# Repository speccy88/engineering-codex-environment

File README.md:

# Engineering CAD & EDA Workbench

A native Debian 13 toolchain for **ChatGPT / Codex Cloud engineering tasks**: create editable circuits and PCBs, model mechanical parts and enclosures, simulate electrical behavior, and return drawings, renders and project files through chat.

**[Showcase](#project-showcase-555-led-fader) · [Example prompts](#example-prompts-by-workflow) · [Run the tools](#use-an-installed-environment) · [Setup](#installation-and-cloud-publication) · [Validation](#verified-behavior)**

## Project showcase: 555 LED fader

An existing six-LED timer project demonstrates how the tools work together: a KiCad schematic and routed PCB, ngspice waveforms, a fitted FreeCAD enclosure, and assembly renders.

<table>
<tr>
<td width="50%"></td>
<td width="50%"></td>
</tr>
<tr><td><b>Electronic assembly</b><br>5 V supply, NE555 timer, transistor driver and six LEDs on a 70 × 54 mm PCB.</td><td><b>Mechanical integration</b><br>86 × 70 × 23 mm enclosure with PCB standoffs, a screw-fastened lid and aligned LED openings.</td></tr>
</table>

These images come from the owner's earlier **555 LED Fader Design Files** and **555 LED Fader Enclosure** projects. The design was reconstructed from photographs; circuit values and dimensions include assumptions. Prior project checks reported zero KiCad ERC/DRC errors and zero PCB/enclosure CAD intersections. It has **not been physically tested or test-fitted**. [Image provenance and reproduction notes](docs/showcase/README.md) distinguish those existing results from the new examples below.

## Example prompts by workflow

Copy a prompt into an installed cloud environment and attach any existing design files. Specify dimensions, units, supply voltage, manufacturing constraints and preferred formats where relevant. Each workflow can be used independently.

### Schematics, PCB layout and routing

**KiCad · SKiDL · Freerouting** — editable schematics and boards, component placement, routing, electrical/design-rule checks, fabrication files and assembled STEP exports.

```text
Design a 5 V, six-LED fader using a 555 timer and a transistor driver.
Use a 70 × 54 mm two-layer PCB with through-hole components. Draw a clean
schematic with readable labels and no overlapping symbols. Explain the
component choices and assumptions, route the board, and run ERC, DRC and
schematic/PCB net checks. Return the editable KiCad project, Gerbers, drill
files, BOM, assembled STEP, preview images and a validation report in a ZIP.
```

For an existing board, ask to preserve its outline, connectors and design rules. Freerouting supplies a DSN → SES routing workflow; imported routes must still pass KiCad checks. [EDA workflow](docs/eda.md)

### Fritzing projects and custom components

**Fritzing · Python layout generator** — self-contained `.fzz` projects, `.fzpz` custom parts, schematic/breadboard/PCB views, native renders and Gerber/drill export.

<table>
<tr>
<td width="50%"></td>
<td width="50%"></td>
</tr>
<tr><td>Breadboard view</td><td>Routed PCB view</td></tr>
</table>

```text
Create a Fritzing project for a 5 V connector, a 330 ohm resistor and a red
LED. Use through-hole parts and a single copper layer. Generate any custom
parts with explicit pin mappings. Keep symbols and labels clear, route
around obstacles, and check overlaps, route clearances and connectivity.
Return the design JSON, editable FZZ, FZPZ parts, PNG/SVG previews of all
three views, Gerber/drill files and the validation report.
```

Try the checked-in [editable project](examples/fritzing/verified/led-series.fzz) or [complete example bundle](examples/fritzing/verified/led-series.zip). The generator supports a documented through-hole, single-layer subset. Its layout checks are **not native Fritzing DRC or electrical ERC**; a schematic-style breadboard view is not a verified physical breadboard assembly. [Fritzing workflow and limits](docs/fritzing.md)

### Parametric parts and PCB enclosures

**FreeCAD · CadQuery · build123d · OpenSCAD** — constrained sketches, editable parameters, solid modeling, STEP/STL export and geometry checks.

<table>
<tr>
<td width="50%"></td>
<td width="50%"></td>
</tr>
<tr><td><b>Parametric bracket</b><br>70 × 40 × 25 mm; three fully constrained sketches, one valid solid and checked export roundtrips.</td><td><b>PCB enclosure</b><br>2.4 mm walls, floor and lid; six recessed LED openings and internal mounting features.</td></tr>
</table>

```text
Create a parametric L-bracket in FreeCAD: 70 mm wide, 40 mm deep, 25 mm
high, with a 3 mm base and flange. Add two 6 mm mounting holes at (10, 15)
and (60, 15) mm, measured from the outer rear-left base corner, with the
flange along the rear edge. Fully constrain the sketches and expose the
main dimensions. Check solid validity, dimensions
and export roundtrips. Return FCStd, STEP, STL, the generator and a render.
```

```text
Design a screw-lid enclosure around the attached PCB STEP and mounting-hole
coordinates. Use 2.4 mm walls, 1 mm nominal clearance to the component
and board envelope, PCB standoffs, and openings aligned with the LEDs and
connector. State print-fit allowances separately. Check interference and
access, then return parametric FCStd, STEP, print-oriented watertight STLs,
a dimensioned drawing, assembled/exploded renders and the check results.
```

For code-first CAD, request a parameterized CadQuery/build123d Python file or an OpenSCAD `.scad` file. Preserve that source alongside STEP/STL. [Mechanical workflow](docs/freecad.md)

### Dimensioned technical drawings

**FreeCAD TechDraw** — drawings linked to native geometry, with PDF and SVG exports.

This drawing was exported from the acceptance fixture: 70 mm overall width and 37 mm exposed base depth. Its dimension references and exported text were checked against the model.

```text
Make a dimensioned A4 drawing from the attached FreeCAD part. Include front,
top and isometric views, overall dimensions, hole diameters and hole-center
distances. Use millimetres and a stated scale. Keep dimensions linked to
the model, check every displayed value and inspect for clipping or overlaps.
Return the FCStd with its TechDraw page, a PDF and an SVG.
```

### Circuit simulation and numerical checks

**ngspice · NumPy · SciPy · Matplotlib** — DC/transient analysis, parameter sweeps, plots and numerical comparisons.

<table>
<tr>
<td width="50%"></td>
<td width="50%"></td>
</tr>
<tr><td><b>555 fader model</b><br>Nominal prediction: 7.46 s cycle and 3.57 mA peak per LED at 5 V and 25 °C.</td><td><b>RC reference check</b><br>573 simulated samples; maximum absolute error of 13.37 µV against the analytic response.</td></tr>
</table>

```text
Simulate the attached 555 LED-fader netlist at 4.5 V, 5 V and 5.5 V.
Sweep timing-capacitor tolerance and transistor gain. Plot timing voltage,
LED current and supply current; calculate cycle time and peak currents.
Flag stalled oscillation and explain model assumptions. Return the SPICE
netlist/models, sweep script, CSV results, plots and a concise report.
```

The 555 plots are model predictions, not measurements; its earlier low-gain stress case stalled. The RC example was rerun with native ngspice for this showcase. [Simulation and scientific Python](docs/python.md)

### Assembly rendering and short animations

**Blender · FFmpeg · ImageMagick** — CPU renders from actual CAD meshes, editable scenes, exploded views and short encoded animations. The assembly and bracket images above demonstrate the visual output.

```text
Render the attached CAD assembly with its actual geometry and units. Use
FreeCAD to tessellate STEP for Blender. Create assembled and exploded views
with clear lighting, a neutral background and all parts inside the frame.
Also make a short turntable MP4. Return the editable Blender scene, render
script, PNGs and MP4. Verify framing and the encoded video's dimensions,
frame count and duration. Preserve the original CAD files separately.
```

Still rendering and a small scripted animation/H.264 fixture are tested. This does not demonstrate physical motion solving or GPU rendering. [Rendering workflow](docs/rendering.md)

**More ideas:** [repair an existing PCB, make a parameterized OpenSCAD part, generate a tetrahedral mesh, compare design variants, or package a handoff](docs/example-prompts.md).

## Use an installed environment

```sh
cd /workspace/engineering-codex-environment
bash setup/verify.sh --quick
```

Use the existing installation for each task. Tools work independently; no fixed parts catalog, project architecture, persistent service, container or interactive desktop is required.

| Task | Entry point | Runtime |
| --- | --- | --- |
| CadQuery/build123d/OCP, scientific Python, Gmsh, SKiDL | `scripts/run-python.sh script.py` | Isolated Python 3.12 |
| FreeCAD native FCStd and solids | `scripts/run-freecad.sh script.py` | System Python 3.13 |
| FreeCAD TechDraw PDF/SVG | `scripts/run-freecad.sh --gui script.py` | Python + temporary Xvfb |
| KiCad checks/exports | `scripts/run-kicad.sh cli ...` | KiCad 9 CLI |
| Programmatic PCB creation/modification | `scripts/run-kicad.sh python script.py` | System Python + legacy pcbnew |
| Official KiCad IPC client | `scripts/run-kicad-ipc.sh script.py` | Separate client; needs live server |
| SPICE simulation | `scripts/run-ngspice.sh -b circuit.cir` | Native ngspice |
| DSN to SES autorouting | `scripts/run-freerouting.sh -de board.dsn -do board.ses` | Freerouting + Java 21 |
| Fritzing generation and routing | `python3 scripts/fritzing-project.py generate design.json --output NEW_DIRECTORY` | Standard-library Python |
| Fritzing SVG/PNG and Gerber/drill | `python3 scripts/fritzing-export.py project.fzz --output NEW_DIRECTORY --png` | Fritzing + Qt offscreen |
| Rendering | `scripts/run-blender.sh script.py ...` | Blender embedded Python |
| Constructive solid geometry | `openscad -o model.stl model.scad` | Native OpenSCAD |

Read [AGENTS.md](AGENTS.md), [toolchain](docs/toolchain.md), [independent workflows](docs/project-workflows.md), and focused [skills](skills/). Keep project source in its own repository and retain editable native files alongside neutral exports. See the [file-format guide](docs/file-formats.md).

## Verified behavior

The combined acceptance run on **2026-11-09** executed **30 commands: 12 runtime/asset probes and 18 functional acceptance commands, all passed**. A separate scientific suite ran **6 pytest tests, all passed**. Fritzing was added and validated separately on **2026-11-10**. See the [test matrix and limitations](setup/test-matrix.md), [baseline](setup/environment-report.md), and [exact versions](setup/versions.lock).

<details>
<summary>What the acceptance fixtures exercise</summary>

- FreeCAD: constrained parametric bracket, native reopen/dimension change, STEP/STL roundtrips, dimensioned TechDraw PDF/SVG.
- CadQuery/build123d/OpenSCAD: independent solid creation and validated exports. Gmsh/meshio: positive-volume tetrahedral roundtrip.
- KiCad: editable divider schematic/PCB, ERC 0, real Freerouting DSN/SES import, DRC/parity/unconnected 0, BOM/Gerber/drill and valid assembled STEP.
- ngspice: 2.5 V divider within 1e-8 V; RC transient matched analytic response within 0.01 V.
- Native grounded/fixed-joint solve: disturbance recovery and save/reopen verification. Live KiCad IPC reads actual board footprints, tracks and vias.
- Actual KiCad PCB plus FreeCAD enclosure: 23 valid solids and zero measured interference, native sources and neutral exports.
- Blender: background CPU renders, native save/reopen, nonblank pixels, camera framing and mechanical imports. FFmpeg/ImageMagick still transforms, eight-frame Blender animation and verified H.264 MP4 export.
- Fritzing: generated custom parts/projects, checked layout and routing, native rendering and fabrication export. See [its verification record](examples/fritzing/verified/verification.json).

These are checks on specific fixtures. Each new design requires its own checks.

</details>

```sh
# Full engineering acceptance, separate from inexpensive CI:
bash setup/verify.sh --full
# Fritzing independently:
bash setup/verify.sh --fritzing
# Cheap repository/CI checks (no engineering apps installed):
python3 setup/check_repository.py
```

Generated files and command evidence live under ignored `artifacts/`. Optional [mechanical](examples/mechanical-part/README.md), [electronic](examples/electronic-circuit/README.md), and [PCB/enclosure](examples/pcb-and-enclosure/README.md) fixtures explain regeneration. Bundle a project with `scripts/export-project.sh PROJECT_DIRECTORY /workspace/project.zip`.

## Installation and cloud publication

The baseline machine's major CAD applications were preinstalled; this repository adds isolated hash-locked Python packages, a checksum-locked workspace native prefix, libraries and tested wrappers. [Cloud setup](docs/cloud-environment.md) distinguishes prerequisites, installation, restoration and publication.

`bash setup/install.sh` refreshes required local dependencies without modifying project source or lockfiles; it is **not** an instruction to reinstall on every new task. Save the [cloud Install script](setup/cloud-install.sh) and [Start skill](setup/start-skill.md) in environment settings, review/save, then publish the prepared filesystem. **A commit does not publish an environment.** Fresh-task restoration remains unverified until publication and a subsequent task.

Known limits: standalone `freecadcmd --version` crashes in this distribution (the tested Python wrapper works); API 10-only IPC methods and advanced joint types remain outside validation; Blender denoising is disabled because this build lacks OpenImageDenoise. See the [matrix](setup/test-matrix.md) for optional PySpice status and other limits.

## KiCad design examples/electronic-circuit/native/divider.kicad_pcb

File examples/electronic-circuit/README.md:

# Optional 5 V resistor-divider example

This is a small acceptance fixture, not a required circuit or component catalog.
The editable KiCad sources are in `native/`. Open `divider.kicad_pro` in KiCad9.
R1 and R2 are 10 kΩ. Apply 5 V between J1 pins1(VIN) and2(GND); unloaded pin3(VOUT)
is2.5 V. Pin polarity/net connectivity is independently checked against the
exported schematic XML netlist.

```sh
scripts/run-kicad.sh python tests/test_kicad/board.py
scripts/run-python.sh tests/test_kicad/step_geometry.py
```

This regenerates schematic, board, routing, ERC/DRC reports, BOM, copper Gerbers,
Excellon drill, STEP assembly and SVG previews under `artifacts/eda/`.
No existing user project is overwritten. Native example sources committed here
are a tested checkpoint; generated artifacts are excluded from Git.

Electrical interface:

|J1 pin|Signal|Role|
|---|---|---|
|1|VIN|5 V external source|
|2|GND|Source return|
|3|VOUT|Unloaded divider output|

Mechanical interface: rectangular40×25 mm PCB, thickness1.6 mm, no mounting
holes. Native board XY runs(0,0)–(40,25)mm. STEP reverses the Y axis; exported
assembled bounds measured x0–40,y−25–0,z−1.405–10.135mm, including header.
The example does not imply loading, power dissipation, EMC or manufacturing
qualification beyond its documented ERC/DRC/net connectivity and geometry tests.

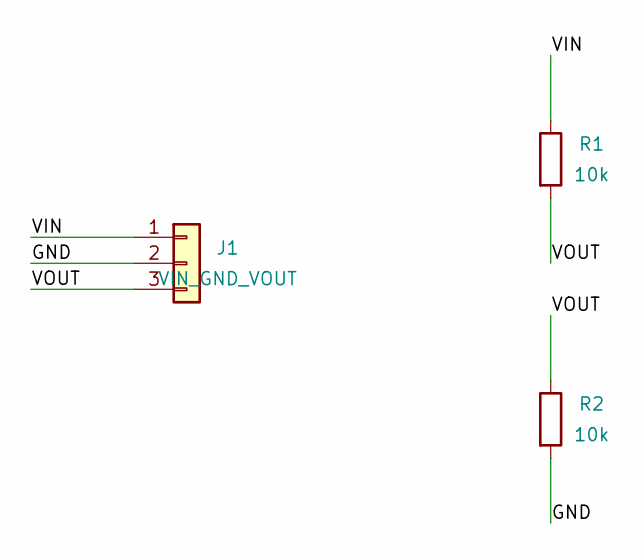
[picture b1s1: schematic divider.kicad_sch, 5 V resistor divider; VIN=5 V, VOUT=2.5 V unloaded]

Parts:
J1: VIN_GND_VOUT; PinHeader_1x03_P2.54mm_Vertical
R1, R2: 10k; R_0805_2012Metric

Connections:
/GND: J1.2, R2.2
/VIN: J1.1, R1.1
/VOUT: J1.3, R1.2, R2.1

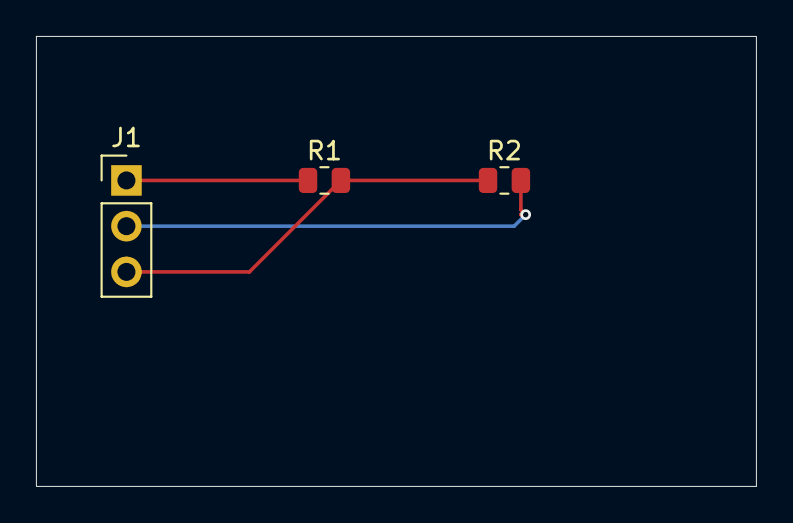
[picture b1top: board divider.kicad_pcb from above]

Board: 2 copper layers, 40.0 x 25.0 mm, 3 parts (0 on the bottom side), 3 nets.
